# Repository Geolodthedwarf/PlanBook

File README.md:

# PlanBook (Collaborative Project)

This repository contains specifications, schematics, PCB and case designs, and firmware source code for the PlanBook laptop.

## License

This project is derived from the PlanBook project. The following licenses are used in the project, unless specified differently in a particular subfolder:

- Schematics, PCBs: [CERN-OHL-S v2](https://www.ohwr.org/project/cernohl/wikis/uploads/002d0b7d5066e6b3829168730237bddb/cern_ohl_s_v2.txt)
- Other documentation, artwork, photos and drawings: [CC-BY-SA 4.0](https://creativecommons.org/licenses/by-sa/4.0/legalcode)
- Software, firmware: Various. [GPL 3.0](https://www.gnu.org/licenses/gpl-3.0.en.html) if not specified otherwise in the file/subdirectory.

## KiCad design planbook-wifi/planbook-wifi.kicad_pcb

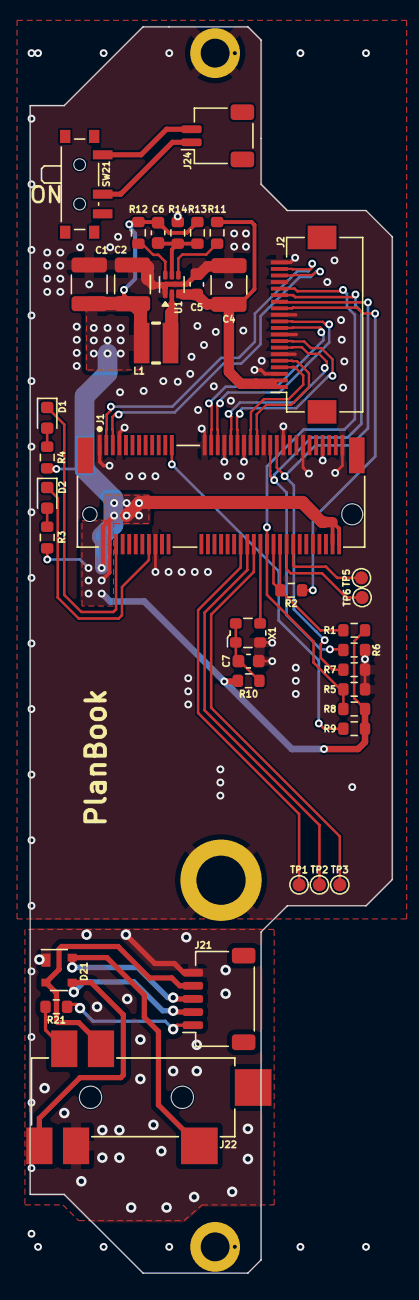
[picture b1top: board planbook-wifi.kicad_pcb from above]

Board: 4 copper layers, 27.6 x 95.0 mm, 41 parts (0 on the bottom side), 40 nets.

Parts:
C1, C2: 47uF; C_1210_3225Metric
C4: 10uF; C_1210_3225Metric
C5: 4.7nF; C_0603_1608Metric
C6: 120pF; C_0603_1608Metric
C7: 0.1uF; C_0603_1608Metric
D1, D2: LED_Small; LED_0603_1608Metric
D21: SP0503BAHT; SOT-143
H1: MountingHole_Pad; Mounting_Sinhoo_SMTSO20
H21, H22: MountingHole_Pad; MountingHole_2.2mm_M2_DIN965_Pad
J1: Bus_M.2_Socket_E; TE_2199119-4
J2: Conn_01x20; Hirose_FH12-20S-0.5SH_1x20-1MP_P0.50mm_Horizontal
J21: CONN_HEAD; JST_SH_SM05B-SRSS-TB_1x05-1MP_P1.00mm_Horizontal
J22: SJ-43516-SMT
J24: CONN_PWRSW; JST_SH_SM02B-SRSS-TB_1x02-1MP_P1.00mm_Horizontal
L1: 220nH 10A; IND-SMD_L3.0-W3.0_FTC303020D
R1, R5, R6, R7, R8, R9: 10k; R_0603_1608Metric
R2, R10, R11: 0; R_0603_1608Metric
R3, R4: 2k; R_0603_1608Metric
R12: 499k; R_0603_1608Metric
R13: 453k; R_0603_1608Metric
R14: 100k; R_0603_1608Metric
R21: 47k; R_0603_1608Metric
SW21: SW_DIP_x01; SW_SPDT_PCM12
TP1, TP2, TP3, TP5, TP6: TestPoint; TestPoint_Pad_D1.0mm
U1: TPS62A04ABDRL; SOT-563
X1: ECS-327MVATX-2-CN-TR3; Oscillator_SMD_ECS_2520MV-xxx-xx-4Pin_2.5x2.0mm

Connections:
+3.3VDAC: J21.1, R21.1
+3V3: C1.1, C2.1, C6.1, J1.2 (3.3V), J1.4 (3.3V), J1.72 (3.3V), J1.74 (3.3V), L1.2, R1.1, R3.1, R4.1, R8.1, R9.1, R10.2, R12.1, R13.1
+5V: C4.1, C5.1, J2.1, J2.2, R11.2, U1.3 (VIN)
GND: C1.2, C2.2, C4.2, C5.2, C7.2, H1.1, H21.1, J1.1 (GND), J1.7 (GND), J1.18 (GND), J1.33 (GND), J1.39 (GND), J1.45 (GND), J1.51 (GND), J1.57 (GND), J1.63 (GND), J1.69 (GND), J1.75 (GND), J2.3, J2.6, J2.9, J2.12, J2.17, J2.20, R5.2, R6.2, R7.2, R14.2, U1.1 (GND), X1.2 (GND)
GNDA: D21.1 (A), J21.5, J22.4 (RING2)
HEAD_DET: J22.6 (RING_SWITCH), R21.2
HEAD_HPL: D21.4 (K), J21.3, J22.2 (TIP)
HEAD_HPR: D21.2 (K), J21.4, J22.3 (RING1)
HEAD_MIC: D21.3 (K), J21.2, J22.1 (SLEEVE)
unnamed: D1.2 (A), R4.2
unnamed: D1.1 (K), J1.6 (~LED_1)
unnamed: D2.2 (A), R3.2
unnamed: D2.1 (K), J1.16 (~LED_2)
unnamed: J1.48 (COEX1), TP3.1
unnamed: J1.46 (COEX2), TP2.1
unnamed: J1.44 (COEX3), TP1.1
unnamed: J1.60 (I2C_CLK), TP5.1
unnamed: J1.58 (I2C_DATA), TP6.1
unnamed: J1.23 (~SDIO_RESET), R9.2
unnamed: J1.54 (~W_DISABLE2), J1.56 (~W_DISABLE1), R1.2, R2.2
unnamed: J24.1, SW21.2
unnamed: J24.2, SW21.1
unnamed: R11.1, U1.4 (EN)
unnamed: C6.2, R13.2, R14.1, U1.5 (FB)
unnamed: R12.2, U1.6 (PG)
unnamed: L1.1, U1.2 (SW)
unnamed: C7.1, R10.1, X1.1 (Tri-State), X1.4 (VDD)
PCIE3_CLK_N: J1.49 (REFCLKn0), J2.5
PCIE3_CLK_P: J1.47 (REFCLKp0), J2.4
PCIE3_RX_N: J1.43 (PERn0), J2.8
PCIE3_RX_P: J1.41 (PERp0), J2.7
PCIE3_TX_N: J1.37 (PETn0), J2.11
PCIE3_TX_P: J1.35 (PETp0), J2.10
RK_WIFI_GPIO0: J1.52 (~PERST0), J2.16, R5.1, R8.2
RK_WIFI_GPIO1: J1.53 (~CLKREQ0), J2.15, R6.1
RK_WIFI_GPIO2: J1.55 (~PEWAKE0), J2.14, R7.1
RK_WIFI_GPIO3: J2.13, R2.1
SUSCLK: J1.50 (SUSCLK), X1.3 (OUT)
USB_N: J1.5 (USB_D-), J2.18
USB_P: J1.3 (USB_D+), J2.19

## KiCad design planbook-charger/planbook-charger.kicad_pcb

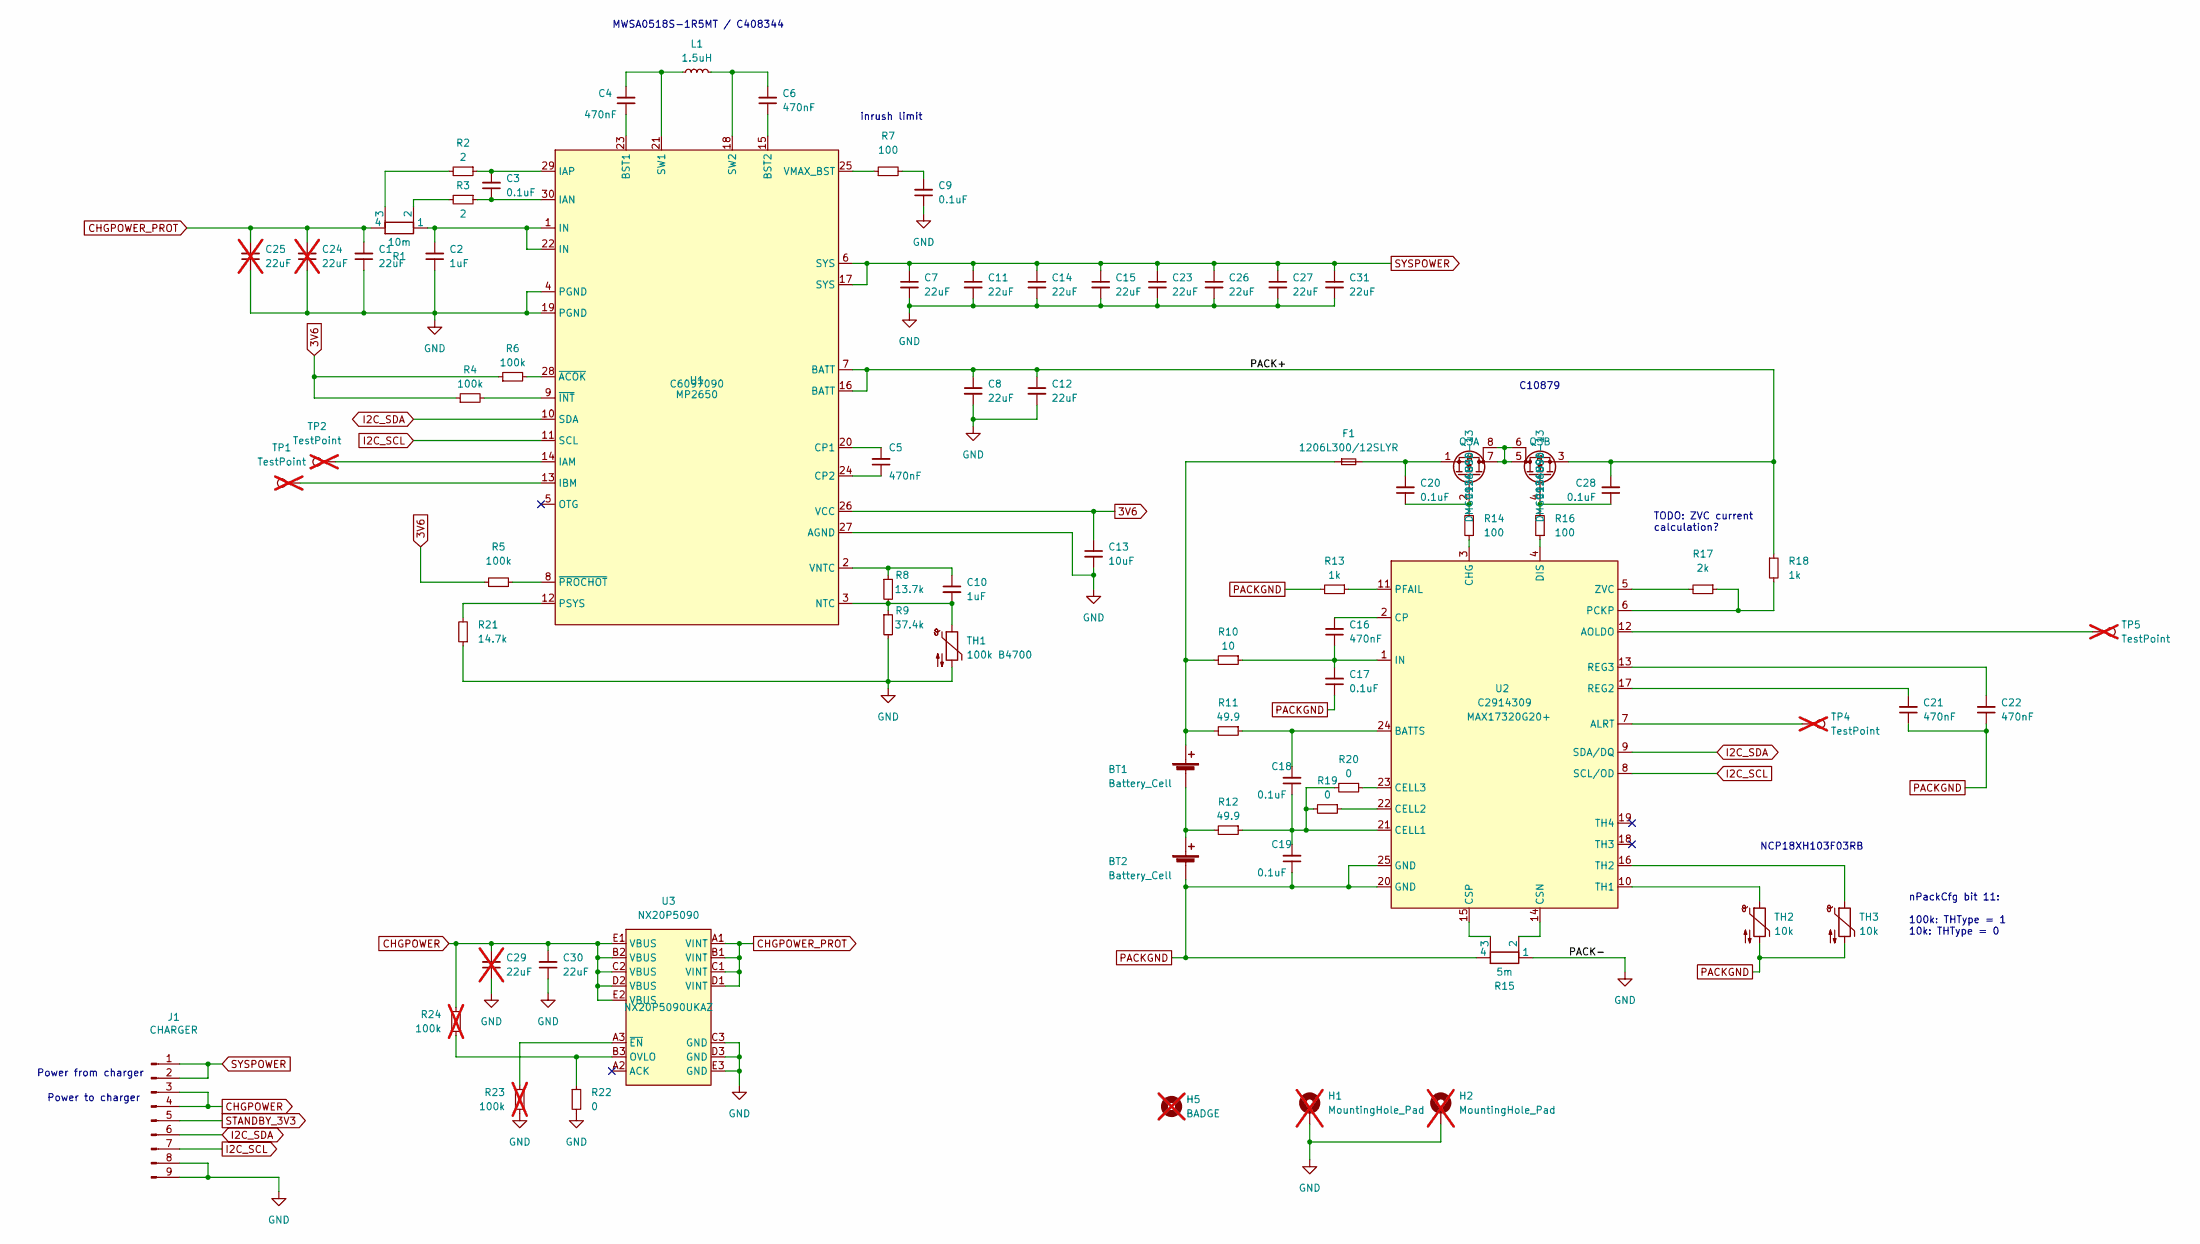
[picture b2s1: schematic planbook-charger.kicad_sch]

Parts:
BT1, BT2: Battery_Cell; JST_PH_S2B-PH-SM4-TB_1x02-1MP_P2.00mm_Horizontal; LCSC C295747
C1, C7, C8, C11, C12, C14, C15, C23, C26, C27, C30, C31: 22uF; C_0805_2012Metric; LCSC C86816
C2, C10: 1uF; C_0603_1608Metric; LCSC C15849
C3, C9, C17, C18, C19, C20, C28: 0.1uF; C_0603_1608Metric; LCSC C14663
C4, C5, C6, C16, C21, C22: 470nF; C_0603_1608Metric; LCSC C2905413
C13: 10uF; C_0603_1608Metric; LCSC C386081
C24, C25, C29: 22uF; C_0805_2012Metric; LCSC C86816; not fitted
F1: 1206L300/12SLYR; Fuse_1206_3216Metric; LCSC C1512052
H1, H2: MountingHole_Pad; MountingHole_2.2mm_M2_Pad; not fitted
H5: BADGE; not fitted
J1: CHARGER; JST_PH_S9B-PH-SM4-TB_1x09-1MP_P2.00mm_Horizontal; LCSC C395365
L1: 1.5uH; L_Sunlord_MWSA0518_5.4x5.2mm; LCSC C408344
Q3: Q_Dual_NMOS_S1G1S2G2D2D2D1D1; SOIC-8_3.9x4.9mm_P1.27mm; LCSC C154896
R1: 10m; R_1206_3216Metric_Kelvin; LCSC C2961483
R2, R3: 2; R_0603_1608Metric; LCSC C22977
R4, R5, R6: 100k; R_0603_1608Metric; LCSC C189597
R7, R14, R16: 100; R_0603_1608Metric; LCSC C384296
R8: 13.7k; R_0603_1608Metric; LCSC C22793
R9: 37.4k; R_0603_1608Metric; LCSC C23033
R10: 10; R_0603_1608Metric; LCSC C22859
R11, R12: 49.9; R_1206_3216Metric; LCSC C4014562
R13, R18: 1k; R_0603_1608Metric; LCSC C112433
R15: 5m; R_1206_3216Metric_Kelvin; LCSC C2988648
R17: 2k; R_0603_1608Metric; LCSC C163843
R19, R20, R22: 0; R_0603_1608Metric
R21: 14.7k; R_0603_1608Metric; LCSC C22874
R23, R24: 100k; R_0603_1608Metric; LCSC C189597; not fitted
TH1: 100k B4700; R_0603_1608Metric; LCSC C14663
TH2, TH3: 10k; R_0603_1608Metric; LCSC C13564
TP1, TP2, TP4, TP5: TestPoint; TestPoint_Pad_1.0x1.0mm; not fitted
U1: MP2650; MP2762A; LCSC C6097090
U2: MAX17320G20+; QFN-24-1EP_4x4mm_P0.5mm_EP2.65x2.65mm_ThermalVias; LCSC C2914309
U3: NX20P5090; NXP_NX20P5090; LCSC C2802659

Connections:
3V6: C13.1, R4.1, R5.1, R6.1, U1.26 (VCC)
/PACK+: C8.1, C12.1, C28.2, Q3.3 (S), R18.1, U1.7 (BATT), U1.16 (BATT)
CHGPOWER: C29.2, C30.2, J1.3, J1.4, R24.2, U3.B2 (VBUS), U3.C2 (VBUS), U3.D2 (VBUS), U3.E1 (VBUS), U3.E2 (VBUS)
CHGPOWER_PROT: C1.2, C24.2, C25.2, R1.4, U3.A1 (VINT), U3.B1 (VINT), U3.C1 (VINT), U3.D1 (VINT)
GND: C1.1, C2.1, C7.2, C8.2, C9.1, C11.2, C12.2, C13.2, C14.2, C15.2, C23.2, C24.1, C25.1, C26.2, C27.2, C29.1, C30.1, C31.2, H1.1, H2.1, J1.8, J1.9, R9.2, R15.1, R21.1, R22.2, R23.1, TH1.2, U1.4 (PGND), U1.19 (PGND), U1.27 (AGND), U3.C3 (GND), U3.D3 (GND), U3.E3 (GND)
I2C_SCL: J1.7, U1.11 (SCL), U2.8 (SCL/OD)
I2C_SDA: J1.6, U1.10 (SDA), U2.9 (SDA/DQ)
unnamed: BT1.1 (+), F1.1, R10.2, R11.2
unnamed: BT1.2 (-), BT2.1 (+), R12.2
unnamed: C2.2, R1.1, U1.1 (IN), U1.22 (IN)
unnamed: C9.2, R7.2
unnamed: Q3.5 (D), Q3.6 (D), Q3.7 (D), Q3.8 (D)
unnamed: C20.1, Q3.2 (G), R14.2
unnamed: C20.2, F1.2, Q3.1 (S)
unnamed: C28.1, Q3.4 (G), R16.2
unnamed: R1.2, R3.2
unnamed: R1.3, R2.2
unnamed: C4.1, U1.23 (BST1)
unnamed: C6.1, U1.15 (BST2)
unnamed: C5.2, U1.20 (CP1)
unnamed: C5.1, U1.24 (CP2)
unnamed: TP2.1, U1.14 (IAM)
unnamed: C3.1, R3.1, U1.30 (IAN)
unnamed: C3.2, R2.1, U1.29 (IAP)
unnamed: TP1.1, U1.13 (IBM)
unnamed: C10.2, R8.2, R9.1, TH1.1, U1.3 (NTC)
unnamed: R21.2, U1.12 (PSYS)
unnamed: C4.2, L1.1, U1.21 (SW1)
unnamed: C6.2, L1.2, U1.18 (SW2)
unnamed: R7.1, U1.25 (VMAX_BST)
unnamed: C10.1, R8.1, U1.2 (VNTC)
unnamed: R6.2, U1.28 (~ACOK)
unnamed: R4.2, U1.9 (~INT)
unnamed: R5.2, U1.8 (~PROCHOT)
unnamed: TP4.1, U2.7 (ALRT)
unnamed: TP5.1, U2.12 (AOLDO)
unnamed: C18.2, R11.1, U2.24 (BATTS)
unnamed: C18.1, C19.2, R12.1, R19.2, R20.2, U2.21 (CELL1)
unnamed: R19.1, U2.22 (CELL2)
unnamed: R20.1, U2.23 (CELL3)
unnamed: R14.1, U2.3 (CHG)
unnamed: C16.2, U2.2 (CP)
unnamed: R15.2, U2.14 (CSN)
unnamed: R15.3, U2.15 (CSP)
unnamed: R16.1, U2.4 (DIS)
unnamed: C16.1, C17.2, R10.1, U2.1 (IN)
unnamed: R17.1, R18.2, U2.6 (PCKP)
unnamed: R13.1, U2.11 (PFAIL)
unnamed: C21.2, U2.17 (REG2)
unnamed: C22.2, U2.13 (REG3)
unnamed: TH2.1, U2.10 (TH1)
unnamed: TH3.1, U2.16 (TH2)
unnamed: R17.2, U2.5 (ZVC)
unnamed: R22.1, R24.1, U3.B3 (OVLO)
unnamed: R23.2, U3.A3 (~EN)
PACKGND: BT2.2 (-), C17.1, C19.1, C21.1, C22.1, R13.2, R15.4, TH2.2, TH3.2, U2.20 (GND), U2.25 (GND)
STANDBY_3V3: J1.5
SYSPOWER: C7.1, C11.1, C14.1, C15.1, C23.1, C26.1, C27.1, C31.1, J1.1, J1.2, U1.6 (SYS), U1.17 (SYS)

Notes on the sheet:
MWSA0518S-1R5MT / C408344
TODO: ZVC current calculation?
C10879
NCP18XH103F03RB
inrush limit
Power from charger
nPackCfg bit 11: 100k: THType = 1 10k: THType = 0
Power to charger

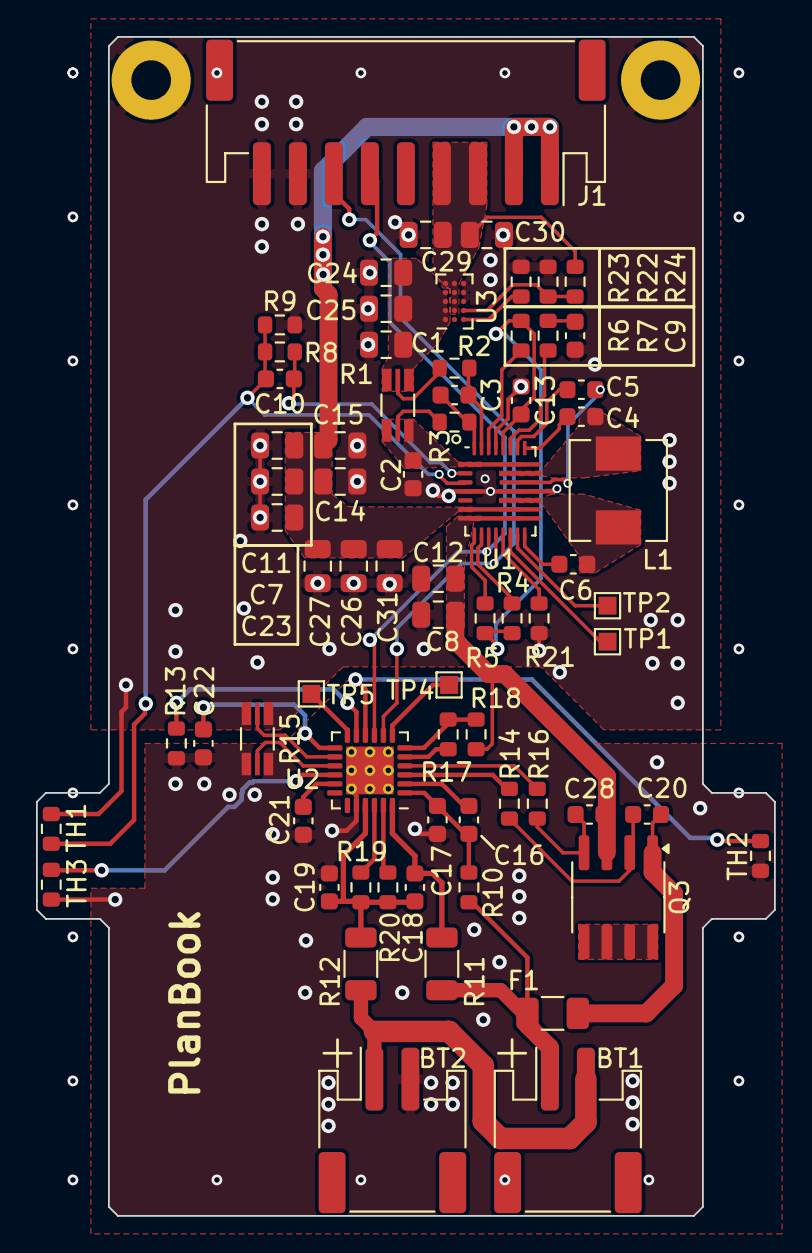
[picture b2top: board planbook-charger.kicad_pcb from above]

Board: 4 copper layers, 41.0 x 65.5 mm, 73 parts (0 on the bottom side), 57 nets.

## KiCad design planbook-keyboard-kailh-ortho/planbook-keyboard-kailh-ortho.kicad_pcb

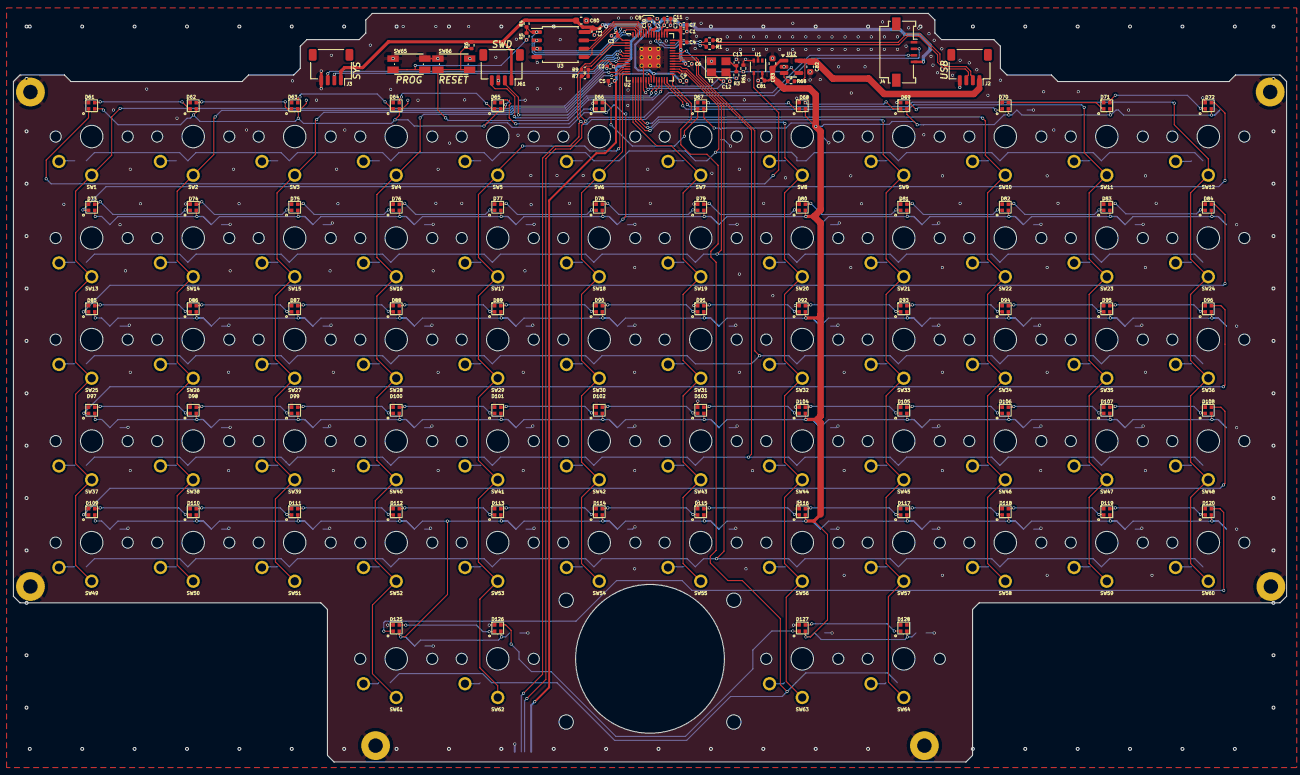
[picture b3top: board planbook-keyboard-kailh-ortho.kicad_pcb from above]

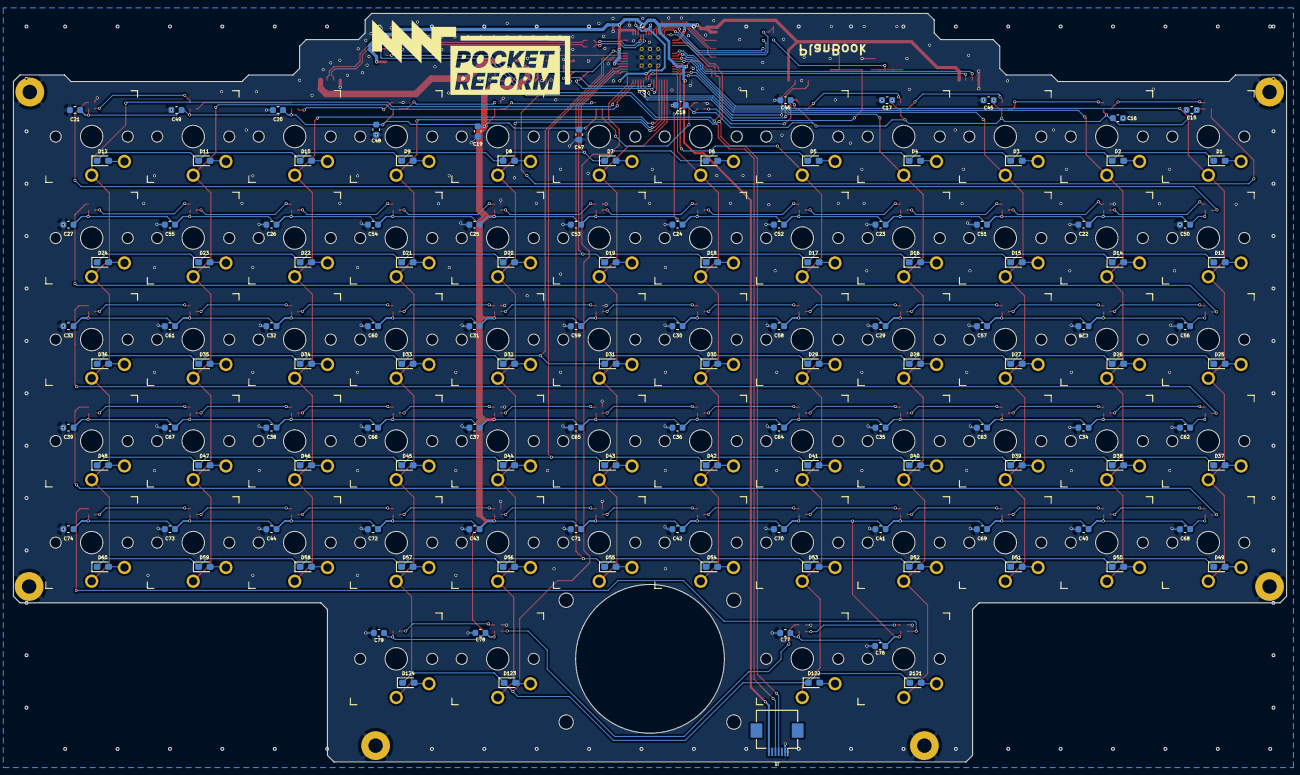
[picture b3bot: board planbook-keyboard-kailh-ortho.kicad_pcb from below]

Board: 4 copper layers, 194.4 x 114.3 mm, 308 parts (130 on the bottom side), 175 nets.

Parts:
C1, C2, C3, C4, C5, C6, C8, C9, C10, C11, C14, C81: 0.1uF; C_0402_1005Metric
C7, C75: 1uF; C_0402_1005Metric
C12, C13: 15pF; C_0402_1005Metric
C15, C16, C17, C18, C19, C20, C21, C22, C23, C24, C25, C26, C27, C28, C29, C30, C31, C32, C33, C34, C35, C36, C37, C38, C39, C40, C41, C42, C43, C44, C45, C46, C47, C48, C49, C50, C51, C52, C53, C54, C55, C56, C57, C58, C59, C60, C61, C62, C63, C64, C65, C66, C67, C68, C69, C70, C71, C72, C73, C74, C76, C77, C78, C79: 0.1uF; C_0603_1608Metric
C80, C82, C83: 10uF; C_0603_1608Metric
D1, D2, D3, D4, D5, D6, D7, D8, D9, D10, D11, D12, D13, D14, D15, D16, D17, D18, D19, D20, D21, D22, D23, D24, D25, D26, D27, D28, D29, D30, D31, D32, D33, D34, D35, D36, D37, D38, D39, D40, D41, D42, D43, D44, D45, D46, D47, D48, D49, D50, D51, D52, D53, D54, D55, D56, D57, D58, D59, D60, D121, D122, D123, D124: MMDL914T1G; D_0603_1608Metric_Pad1.05x0.95mm_HandSolder
D61, D62, D63, D64, D65, D66, D67, D68, D69, D70, D71, D72, D73, D74, D75, D76, D77, D78, D79, D80, D81, D82, D83, D84, D85, D86, D87, D88, D89, D90, D91, D92, D93, D94, D95, D96, D97, D98, D99, D100, D101, D102, D103, D104, D105, D106, D107, D108, D109, D110, D111, D112, D113, D114, D115, D116, D117, D118, D119, D120, D125, D126, D127, D128: SK6805-EC15
GFX1: PlanBook; planbook
H1: MH1; MountingHole_2.2mm_M2_Pad
H2: MH2; MountingHole_2.2mm_M2_Pad
H3: MH3; MountingHole_2.2mm_M2_Pad
H4: MH4; MountingHole_2.2mm_M2_Pad
H5: MH5; MountingHole_2.2mm_M2_Pad
H6: MH6; MountingHole_2.2mm_M2_Pad
H7, H8, H9, H10: TBH; MountingHole_2.2mm_M2
J1: Conn_01x06_Female; Hirose_FH12-6S-0.5SH_1x06-1MP_P0.50mm_Horizontal
J2: USB; JST_SH_SM04B-SRSS-TB_1x04-1MP_P1.00mm_Horizontal
J3, J61: UART; JST_SH_SM04B-SRSS-TB_1x04-1MP_P1.00mm_Horizontal
J4: AUX; Molex_200528-0040_1x04-1MP_P1.00mm_Horizontal
R1, R2: 27.4; R_0402_1005Metric
R3, R5: 1k; R_0402_1005Metric
R4, R6, R61, R68: 10k; R_0402_1005Metric
R7, R9: 4.7k; R_0402_1005Metric
SW1, SW2, SW3, SW4, SW5, SW6, SW7, SW8, SW9, SW10, SW11, SW12, SW13, SW14, SW15, SW16, SW17, SW18, SW19, SW20, SW21, SW22, SW23, SW24, SW25, SW26, SW27, SW28, SW29, SW30, SW31, SW32, SW33, SW34, SW35, SW36, SW37, SW38, SW39, SW40, SW41, SW42, SW43, SW44, SW45, SW46, SW47, SW48, SW49, SW50, SW51, SW52, SW53, SW54, SW55, SW56, SW57, SW58, SW59, SW60, SW61, SW62, SW63, SW64: Choc; PG1350
SW65: SW_HWB; Diptronics-PTLP2
SW66: SW_RST; Diptronics-PTLP2
U1: SN74LV1T34DCK; SOT-353_SC-70-5
U2: RP2040; RP2040-QFN-56
U3: W25Q32JVSS; SOIC-8_5.23x5.23mm_P1.27mm
U12: AP22815A; SOT-23-5
Y1: 12MHz 12pF; Crystal_SMD_3225-4Pin_3.2x2.5mm

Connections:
+1V1: C9.1, C10.1, C11.1, C75.1, U2.23 (DVDD), U2.45 (VREG_VOUT), U2.50 (DVDD)
+3V3: C1.1, C2.1, C3.1, C4.1, C5.1, C6.1, C7.1, C8.1, C14.1, C80.1, J1.6, J3.1, J4.4, J61.1, R4.1, R6.1, R7.2, R9.2, U2.1 (IOVDD), U2.10 (IOVDD), U2.22 (IOVDD), U2.33 (IOVDD), U2.42 (IOVDD), U2.43 (ADC_AVDD), U2.44 (VREG_IN), U2.48 (USB_VDD), U2.49 (IOVDD), U3.8 (VCC)
+5V: C82.1, J2.1, R68.2, U12.5 (IN)
/PlanBook KBD MCU/UD+: R1.2, U2.47 (USB_DP)
/PlanBook KBD MCU/UD-: R2.1, U2.46 (USB_DM)
COL1: SW1.1, SW13.1, SW25.1, SW37.1, SW49.1, U2.8 (GPIO6)
COL2: SW2.1, SW14.1, SW26.1, SW38.1, SW50.1, U2.9 (GPIO7)
COL3: SW3.1, SW15.1, SW27.1, SW39.1, SW51.1, U2.11 (GPIO8)
COL4: SW4.1, SW16.1, SW28.1, SW40.1, SW52.1, SW61.1, U2.12 (GPIO9)
COL5: SW5.1, SW17.1, SW29.1, SW41.1, SW53.1, SW62.1, U2.13 (GPIO10)
COL6: SW6.1, SW18.1, SW30.1, SW42.1, SW54.1, U2.14 (GPIO11)
COL7: SW7.1, SW19.1, SW31.1, SW43.1, SW55.1, U2.15 (GPIO12)
COL8: SW8.1, SW20.1, SW32.1, SW44.1, SW56.1, SW63.1, U2.16 (GPIO13)
COL9: SW9.1, SW21.1, SW33.1, SW45.1, SW57.1, SW64.1, U2.17 (GPIO14)
COL10: SW10.1, SW22.1, SW34.1, SW46.1, SW58.1, U2.18 (GPIO15)
COL11: SW11.1, SW23.1, SW35.1, SW47.1, SW59.1, U2.27 (GPIO16)
COL12: SW12.1, SW24.1, SW36.1, SW48.1, SW60.1, U2.28 (GPIO17)
D+: J2.3, R1.1
D-: J2.2, R2.2
GND: C1.2, C2.2, C3.2, C4.2, C5.2, C6.2, C7.2, C8.2, C9.2, C10.2, C11.2, C12.2, C13.2, C14.2, C15.2, C16.2, C17.2, C18.2, C19.2, C20.2, C21.2, C22.2, C23.2, C24.2, C25.2, C26.2, C27.2, C28.2, C29.2, C30.2, C31.2, C32.2, C33.2, C34.2, C35.2, C36.2, C37.2, C38.2, C39.2, C40.2, C41.2, C42.2, C43.2, C44.2, C45.2, C46.2, C47.2, C48.2, C49.2, C50.2, C51.2, C52.2, C53.2, C54.2, C55.2, C56.2, C57.2, C58.2, C59.2, C60.2, C61.2, C62.2, C63.2, C64.2, C65.2, C66.2, C67.2, C68.2, C69.2, C70.2, C71.2, C72.2, C73.2, C74.2, C75.2, C76.2, C77.2, C78.2, C79.2, C80.2, C81.2, C82.2, C83.2, D61.4 (VSS), D62.4 (VSS), D63.4 (VSS), D64.4 (VSS), D65.4 (VSS), D66.4 (VSS), D67.4 (VSS), D68.4 (VSS), D69.4 (VSS), D70.4 (VSS), D71.4 (VSS), D72.4 (VSS), D73.4 (VSS), D74.4 (VSS), D75.4 (VSS), D76.4 (VSS), D77.4 (VSS), D78.4 (VSS), D79.4 (VSS), D80.4 (VSS), D81.4 (VSS), D82.4 (VSS), D83.4 (VSS), D84.4 (VSS), D85.4 (VSS), D86.4 (VSS), D87.4 (VSS), D88.4 (VSS), D89.4 (VSS), D90.4 (VSS), D91.4 (VSS), D92.4 (VSS), D93.4 (VSS), D94.4 (VSS), D95.4 (VSS), D96.4 (VSS), D97.4 (VSS), D98.4 (VSS), D99.4 (VSS), D100.4 (VSS), D101.4 (VSS), D102.4 (VSS), D103.4 (VSS), D104.4 (VSS), D105.4 (VSS), D106.4 (VSS), D107.4 (VSS), D108.4 (VSS), D109.4 (VSS), D110.4 (VSS), D111.4 (VSS), D112.4 (VSS), D113.4 (VSS), D114.4 (VSS), D115.4 (VSS), D116.4 (VSS), D117.4 (VSS), D118.4 (VSS), D119.4 (VSS), D120.4 (VSS), D125.4 (VSS), D126.4 (VSS), D127.4 (VSS), D128.4 (VSS), H1.1, H2.1, H3.1, H4.1, H5.1, H6.1, J1.1, J2.4, J3.4, J4.1, J61.3, R61.1, SW65.2, SW66.2, U1.3 (GND), U2.19 (TESTEN), U2.57 (GND), U3.4 (GND), U12.2 (GND), Y1.2, Y1.4
LED_DATA: U1.2 (A), U2.36 (GPIO24)
LED_POWER: C15.1, C16.1, C17.1, C18.1, C19.1, C20.1, C21.1, C22.1, C23.1, C24.1, C25.1, C26.1, C27.1, C28.1, C29.1, C30.1, C31.1, C32.1, C33.1, C34.1, C35.1, C36.1, C37.1, C38.1, C39.1, C40.1, C41.1, C42.1, C43.1, C44.1, C45.1, C46.1, C47.1, C48.1, C49.1, C50.1, C51.1, C52.1, C53.1, C54.1, C55.1, C56.1, C57.1, C58.1, C59.1, C60.1, C61.1, C62.1, C63.1, C64.1, C65.1, C66.1, C67.1, C68.1, C69.1, C70.1, C71.1, C72.1, C73.1, C74.1, C76.1, C77.1, C78.1, C79.1, C81.1, C83.1, D61.2 (VDD), D62.2 (VDD), D63.2 (VDD), D64.2 (VDD), D65.2 (VDD), D66.2 (VDD), D67.2 (VDD), D68.2 (VDD), D69.2 (VDD), D70.2 (VDD), D71.2 (VDD), D72.2 (VDD), D73.2 (VDD), D74.2 (VDD), D75.2 (VDD), D76.2 (VDD), D77.2 (VDD), D78.2 (VDD), D79.2 (VDD), D80.2 (VDD), D81.2 (VDD), D82.2 (VDD), D83.2 (VDD), D84.2 (VDD), D85.2 (VDD), D86.2 (VDD), D87.2 (VDD), D88.2 (VDD), D89.2 (VDD), D90.2 (VDD), D91.2 (VDD), D92.2 (VDD), D93.2 (VDD), D94.2 (VDD), D95.2 (VDD), D96.2 (VDD), D97.2 (VDD), D98.2 (VDD), D99.2 (VDD), D100.2 (VDD), D101.2 (VDD), D102.2 (VDD), D103.2 (VDD), D104.2 (VDD), D105.2 (VDD), D106.2 (VDD), D107.2 (VDD), D108.2 (VDD), D109.2 (VDD), D110.2 (VDD), D111.2 (VDD), D112.2 (VDD), D113.2 (VDD), D114.2 (VDD), D115.2 (VDD), D116.2 (VDD), D117.2 (VDD), D118.2 (VDD), D119.2 (VDD), D120.2 (VDD), D125.2 (VDD), D126.2 (VDD), D127.2 (VDD), D128.2 (VDD), U1.5 (VCC), U12.1 (OUT)
LED_PWR_EN: R61.2, U2.37 (GPIO25), U12.4 (EN)
unnamed: C13.1, R3.1, Y1.3
unnamed: D1.2 (A), SW1.2
unnamed: D2.2 (A), SW2.2
unnamed: D3.2 (A), SW3.2
unnamed: D4.2 (A), SW4.2
unnamed: D5.2 (A), SW5.2
unnamed: D6.2 (A), SW6.2
unnamed: D7.2 (A), SW7.2
unnamed: D8.2 (A), SW8.2
unnamed: D9.2 (A), SW9.2
unnamed: D10.2 (A), SW10.2
unnamed: D11.2 (A), SW11.2
unnamed: D12.2 (A), SW12.2
unnamed: D13.2 (A), SW13.2
unnamed: D14.2 (A), SW14.2
unnamed: D15.2 (A), SW15.2
unnamed: D16.2 (A), SW16.2
unnamed: D17.2 (A), SW17.2
unnamed: D18.2 (A), SW18.2
unnamed: D19.2 (A), SW19.2
unnamed: D20.2 (A), SW20.2
unnamed: D21.2 (A), SW21.2
unnamed: D22.2 (A), SW22.2
unnamed: D23.2 (A), SW23.2
unnamed: D24.2 (A), SW24.2
unnamed: D25.2 (A), SW25.2
unnamed: D26.2 (A), SW26.2
unnamed: D27.2 (A), SW27.2
unnamed: D28.2 (A), SW28.2
unnamed: D29.2 (A), SW29.2
unnamed: D30.2 (A), SW30.2
unnamed: D31.2 (A), SW31.2
unnamed: D32.2 (A), SW32.2
unnamed: D33.2 (A), SW33.2
unnamed: D34.2 (A), SW34.2
unnamed: D35.2 (A), SW35.2
unnamed: D36.2 (A), SW36.2
unnamed: D37.2 (A), SW37.2
unnamed: D38.2 (A), SW38.2
unnamed: D39.2 (A), SW39.2
unnamed: D40.2 (A), SW40.2
unnamed: D41.2 (A), SW41.2
unnamed: D42.2 (A), SW42.2
unnamed: D43.2 (A), SW43.2
unnamed: D44.2 (A), SW44.2
unnamed: D45.2 (A), SW45.2
unnamed: D46.2 (A), SW46.2
unnamed: D47.2 (A), SW47.2
unnamed: D48.2 (A), SW48.2
unnamed: D49.2 (A), SW49.2
unnamed: D50.2 (A), SW50.2
unnamed: D51.2 (A), SW51.2
unnamed: D52.2 (A), SW52.2
unnamed: D53.2 (A), SW53.2
unnamed: D54.2 (A), SW54.2
unnamed: D55.2 (A), SW55.2
unnamed: D56.2 (A), SW56.2
unnamed: D57.2 (A), SW57.2
unnamed: D58.2 (A), SW58.2
unnamed: D59.2 (A), SW59.2
unnamed: D60.2 (A), SW60.2
unnamed: D61.1 (DIN), U1.4 (Y)
unnamed: D61.3 (DOUT), D62.1 (DIN)
unnamed: D62.3 (DOUT), D63.1 (DIN)
unnamed: D63.3 (DOUT), D64.1 (DIN)
unnamed: D64.3 (DOUT), D65.1 (DIN)
unnamed: D65.3 (DOUT), D66.1 (DIN)
unnamed: D66.3 (DOUT), D67.1 (DIN)
unnamed: D67.3 (DOUT), D68.1 (DIN)
unnamed: D68.3 (DOUT), D69.1 (DIN)
unnamed: D69.3 (DOUT), D70.1 (DIN)
unnamed: D70.3 (DOUT), D71.1 (DIN)
unnamed: D71.3 (DOUT), D72.1 (DIN)
unnamed: D72.3 (DOUT), D73.1 (DIN)
unnamed: D73.3 (DOUT), D74.1 (DIN)
unnamed: D74.3 (DOUT), D75.1 (DIN)
unnamed: D75.3 (DOUT), D76.1 (DIN)
unnamed: D76.3 (DOUT), D77.1 (DIN)
unnamed: D77.3 (DOUT), D78.1 (DIN)
unnamed: D78.3 (DOUT), D79.1 (DIN)
unnamed: D79.3 (DOUT), D80.1 (DIN)
unnamed: D80.3 (DOUT), D81.1 (DIN)
unnamed: D81.3 (DOUT), D82.1 (DIN)
unnamed: D82.3 (DOUT), D83.1 (DIN)
unnamed: D83.3 (DOUT), D84.1 (DIN)
unnamed: D84.3 (DOUT), D85.1 (DIN)
unnamed: D85.3 (DOUT), D86.1 (DIN)
unnamed: D86.3 (DOUT), D87.1 (DIN)
unnamed: D87.3 (DOUT), D88.1 (DIN)
unnamed: D88.3 (DOUT), D89.1 (DIN)
unnamed: D89.3 (DOUT), D90.1 (DIN)
unnamed: D90.3 (DOUT), D91.1 (DIN)
unnamed: D91.3 (DOUT), D92.1 (DIN)
unnamed: D92.3 (DOUT), D93.1 (DIN)
unnamed: D93.3 (DOUT), D94.1 (DIN)
unnamed: D94.3 (DOUT), D95.1 (DIN)
unnamed: D95.3 (DOUT), D96.1 (DIN)
unnamed: D96.3 (DOUT), D97.1 (DIN)
unnamed: D97.3 (DOUT), D98.1 (DIN)
unnamed: D98.3 (DOUT), D99.1 (DIN)
unnamed: D99.3 (DOUT), D100.1 (DIN)
unnamed: D100.3 (DOUT), D101.1 (DIN)
unnamed: D101.3 (DOUT), D102.1 (DIN)
unnamed: D102.3 (DOUT), D103.1 (DIN)
unnamed: D103.3 (DOUT), D104.1 (DIN)
unnamed: D104.3 (DOUT), D105.1 (DIN)
unnamed: D105.3 (DOUT), D106.1 (DIN)
unnamed: D106.3 (DOUT), D107.1 (DIN)
unnamed: D107.3 (DOUT), D108.1 (DIN)
unnamed: D108.3 (DOUT), D109.1 (DIN)
unnamed: D109.3 (DOUT), D110.1 (DIN)
unnamed: D110.3 (DOUT), D111.1 (DIN)
unnamed: D111.3 (DOUT), D112.1 (DIN)
unnamed: D112.3 (DOUT), D113.1 (DIN)
unnamed: D113.3 (DOUT), D114.1 (DIN)
unnamed: D114.3 (DOUT), D115.1 (DIN)
unnamed: D115.3 (DOUT), D116.1 (DIN)
unnamed: D116.3 (DOUT), D117.1 (DIN)
unnamed: D117.3 (DOUT), D118.1 (DIN)
unnamed: D118.3 (DOUT), D119.1 (DIN)
unnamed: D119.3 (DOUT), D120.1 (DIN)
unnamed: D120.3 (DOUT), D125.1 (DIN)
unnamed: D121.2 (A), SW61.2
unnamed: D122.2 (A), SW62.2
unnamed: D123.2 (A), SW63.2
unnamed: D124.2 (A), SW64.2
unnamed: D125.3 (DOUT), D126.1 (DIN)
unnamed: D126.3 (DOUT), D127.1 (DIN)
unnamed: D127.3 (DOUT), D128.1 (DIN)
unnamed: C12.1, U2.20 (XIN), Y1.1
unnamed: R3.2, U2.21 (XOUT)
unnamed: R68.1, U12.3 (FLG)
PROG: R5.1, SW65.1
QSPI_CS: R4.2, R5.2, U2.56 (QSPI_SS), U3.1 (~CS)
QSPI_SCK: U2.52 (QSPI_SCLK), U3.6 (CLK)
QSPI_SD0: U2.53 (QSPI_SD0), U3.5 (DI(IO0))
QSPI_SD1: U2.55 (QSPI_SD1), U3.2 (DO(IO1))
QSPI_SD2: U2.54 (QSPI_SD2), U3.3 (IO2)
QSPI_SD3: U2.51 (QSPI_SD3), U3.7 (IO3)
RESET: R6.2, SW66.1, U2.26 (RUN)
ROW1: D1.1 (K), D2.1 (K), D3.1 (K), D4.1 (K), D5.1 (K), D6.1 (K), D7.1 (K), D8.1 (K), D9.1 (K), D10.1 (K), D11.1 (K), D12.1 (K), U2.30 (GPIO19)
ROW2: D13.1 (K), D14.1 (K), D15.1 (K), D16.1 (K), D17.1 (K), D18.1 (K), D19.1 (K), D20.1 (K), D21.1 (K), D22.1 (K), D23.1 (K), D24.1 (K), U2.31 (GPIO20)
ROW3: D25.1 (K), D26.1 (K), D27.1 (K), D28.1 (K), D29.1 (K), D30.1 (K), D31.1 (K), D32.1 (K), D33.1 (K), D34.1 (K), D35.1 (K), D36.1 (K), U2.35 (GPIO23)
ROW4: D37.1 (K), D38.1 (K), D39.1 (K), D40.1 (K), D41.1 (K), D42.1 (K), D43.1 (K), D44.1 (K), D45.1 (K), D46.1 (K), D47.1 (K), D48.1 (K), U2.34 (GPIO22)
ROW5: D49.1 (K), D50.1 (K), D51.1 (K), D52.1 (K), D53.1 (K), D54.1 (K), D55.1 (K), D56.1 (K), D57.1 (K), D58.1 (K), D59.1 (K), D60.1 (K), U2.32 (GPIO21)
ROW6: D121.1 (K), D122.1 (K), D123.1 (K), D124.1 (K), U2.29 (GPIO18)
SCL: J1.4, J4.3, R7.1, U2.3 (GPIO1)
SDA: J1.3, J4.2, R9.1, U2.2 (GPIO0)
SWC: J61.2, U2.24 (SWCLK)
SWD: J61.4, U2.25 (SWD)
UART_RX: J3.2, U2.7 (GPIO5)
UART_TX: J3.3, U2.6 (GPIO4)

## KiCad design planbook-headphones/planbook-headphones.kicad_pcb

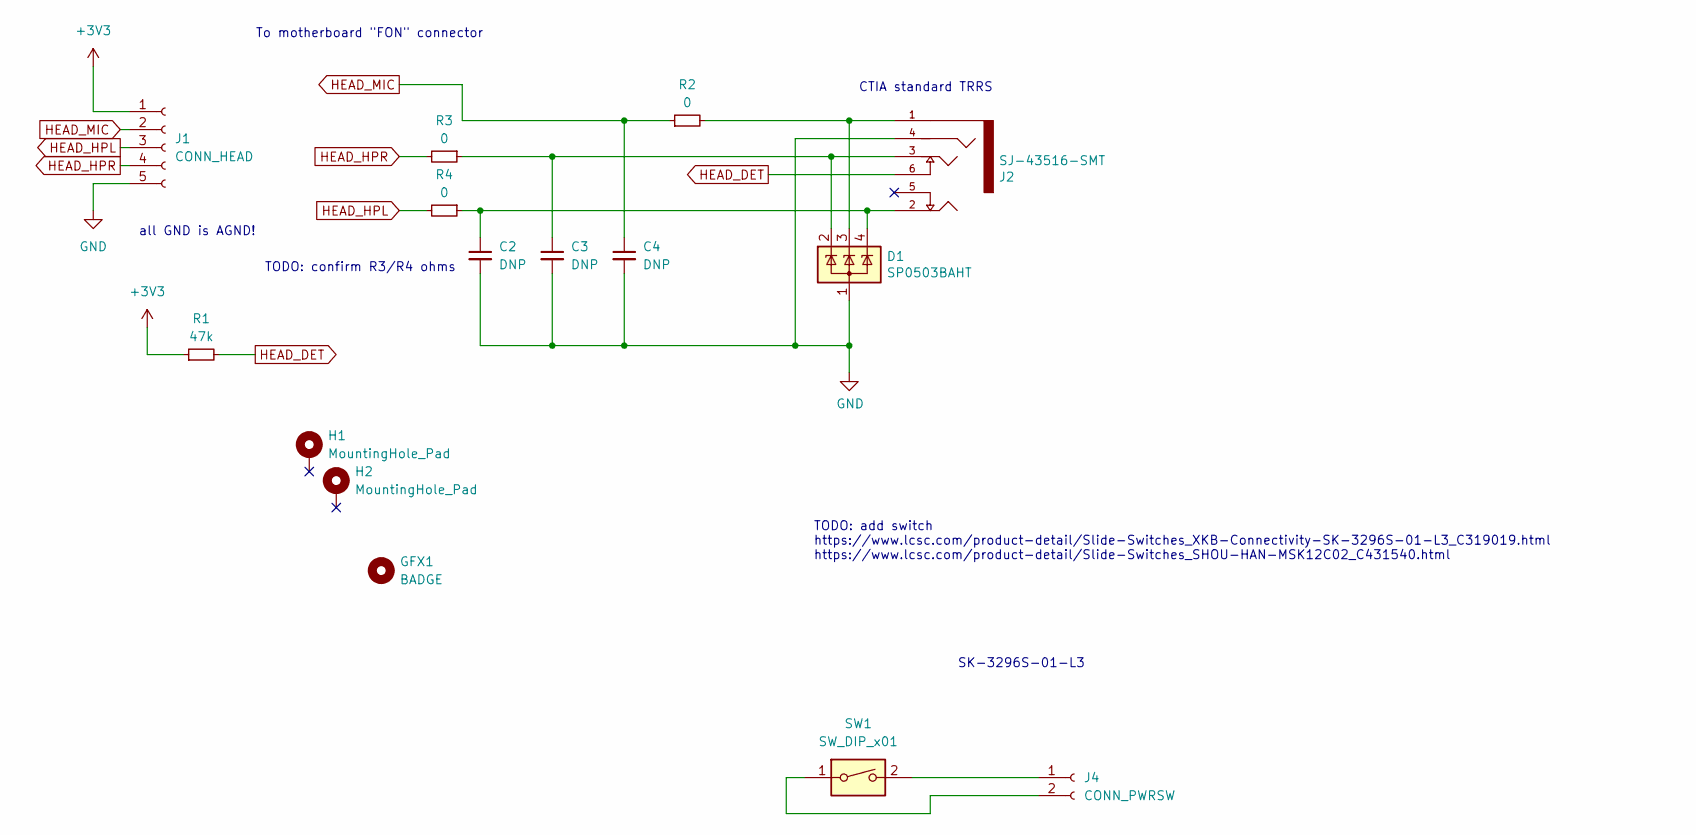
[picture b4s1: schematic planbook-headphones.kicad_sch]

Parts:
C2, C3, C4: DNP; C_0603_1608Metric; LCSC DNP
D1: SP0503BAHT; SOT-143; LCSC C3040626
GFX1: BADGE
H1, H2: MountingHole_Pad; MountingHole_2.2mm_M2_DIN965_Pad
J1: CONN_HEAD; JST_SH_SM05B-SRSS-TB_1x05-1MP_P1.00mm_Horizontal; LCSC C136657
J2: SJ-43516-SMT
J4: CONN_PWRSW; JST_SH_SM02B-SRSS-TB_1x02-1MP_P1.00mm_Horizontal; LCSC C160402
R1: 47k; R_0603_1608Metric
R2, R3, R4: 0; R_0603_1608Metric
SW1: SW_DIP_x01; SW_SPDT_PCM12; LCSC C319019

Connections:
+3V3: J1.1, R1.1
GND: C2.2, C3.2, C4.2, D1.1 (A), J1.5, J2.4 (RING2)
HEAD_DET: J2.6 (RING_SWITCH), R1.2
HEAD_HPL: J1.3, R4.2
HEAD_HPR: J1.4, R3.2
HEAD_MIC: C4.1, J1.2, R2.1
unnamed: C3.1, D1.2 (K), J2.3 (RING1), R3.1
unnamed: D1.3 (K), J2.1 (SLEEVE), R2.2
unnamed: C2.1, D1.4 (K), J2.2 (TIP), R4.1
unnamed: J4.1, SW1.2
unnamed: J4.2, SW1.1

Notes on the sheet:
SK-3296S-01-L3
To motherboard "FON" connector
TODO: add switch https://www.lcsc.com/product-detail/Slide-Switches_XKB-Connectivity-SK-3296S-01-L3_C319019.html https://www.lcsc.com/product-detail/Slide-Switches_SHOU-HAN-MSK12C02_C431540.html
all GND is AGND!
CTIA standard TRRS
TODO: confirm R3/R4 ohms

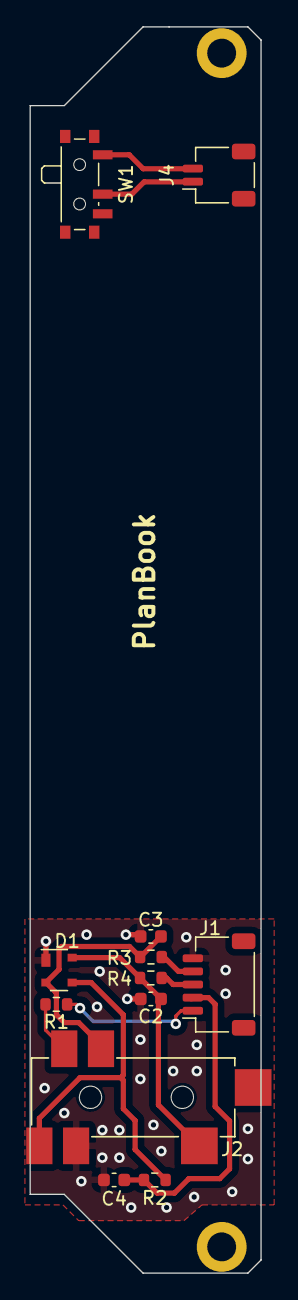
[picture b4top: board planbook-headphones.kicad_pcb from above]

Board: 2 copper layers, 17.6 x 95.0 mm, 14 parts (0 on the bottom side), 11 nets.

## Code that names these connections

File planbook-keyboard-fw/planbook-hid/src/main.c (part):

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  uart_set_format(UART_ID, DATA_BITS, STOP_BITS, PARITY);
  uart_set_hw_flow(UART_ID, false, false);
  uart_set_fifo_enabled(UART_ID, true);
  gpio_set_function(PIN_UART_TX, GPIO_FUNC_UART);
  gpio_set_function(PIN_UART_RX, GPIO_FUNC_UART);
  unsigned int UART_IRQ = UART_ID == uart0 ? UART0_IRQ : UART1_IRQ;

  gpio_init(PIN_LEDS);
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
  /* Configure rows as input and enable pull-downs */
  gpio_init_mask(PIN_ROW_MASK);
  gpio_pull_down(PIN_ROW1);
  gpio_pull_down(PIN_ROW2);
  gpio_pull_down(PIN_ROW3);
  gpio_pull_down(PIN_ROW4);
  gpio_pull_down(PIN_ROW5);
  gpio_pull_down(PIN_ROW6);

  i2c_init(i2c0, 400 * 1000);
  gpio_set_function(PIN_SDA, GPIO_FUNC_I2C);
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    uint32_t rows = 0;

    switch (x) {
    case 0: gpio_put(PIN_COL1, 1); break;
    case 1: gpio_put(PIN_COL2, 1); break;
    case 2: gpio_put(PIN_COL3, 1); break;
    case 3: gpio_put(PIN_COL4, 1); break;
    case 4: gpio_put(PIN_COL5, 1); break;
    case 5: gpio_put(PIN_COL6, 1); break;
    case 6: gpio_put(PIN_COL7, 1); break;
    case 7: gpio_put(PIN_COL8, 1); break;
    case 8: gpio_put(PIN_COL9, 1); break;
    case 9: gpio_put(PIN_COL10, 1); break;
    case 10: gpio_put(PIN_COL11, 1); break;
    case 11: gpio_put(PIN_COL12, 1); break;
    }

    // wait for signal to stabilize
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      uint8_t debounced_pressed = 0;

      switch (y) {
      case 0:  pressed = (rows & (1u<<PIN_ROW1)) != 0; break;
      case 1:  pressed = (rows & (1u<<PIN_ROW2)) != 0; break;
      case 2:  pressed = (rows & (1u<<PIN_ROW3)) != 0; break;
      case 3:  pressed = (rows & (1u<<PIN_ROW4)) != 0; break;
      case 4:  pressed = (rows & (1u<<PIN_ROW5)) != 0; break;
      case 5:  pressed = (rows & (1u<<PIN_ROW6)) != 0; break;
      }

      // shift new state as bit into debounce "register"
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

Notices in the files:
planbook-keyboard-fw/planbook-hid/src/main.c:
SPDX-License-Identifier: GPL-3.0-or-later
Copyright 2021-2025 PlanBook Project
Copyright 2019 Ha Thach (tinyusb.org)
